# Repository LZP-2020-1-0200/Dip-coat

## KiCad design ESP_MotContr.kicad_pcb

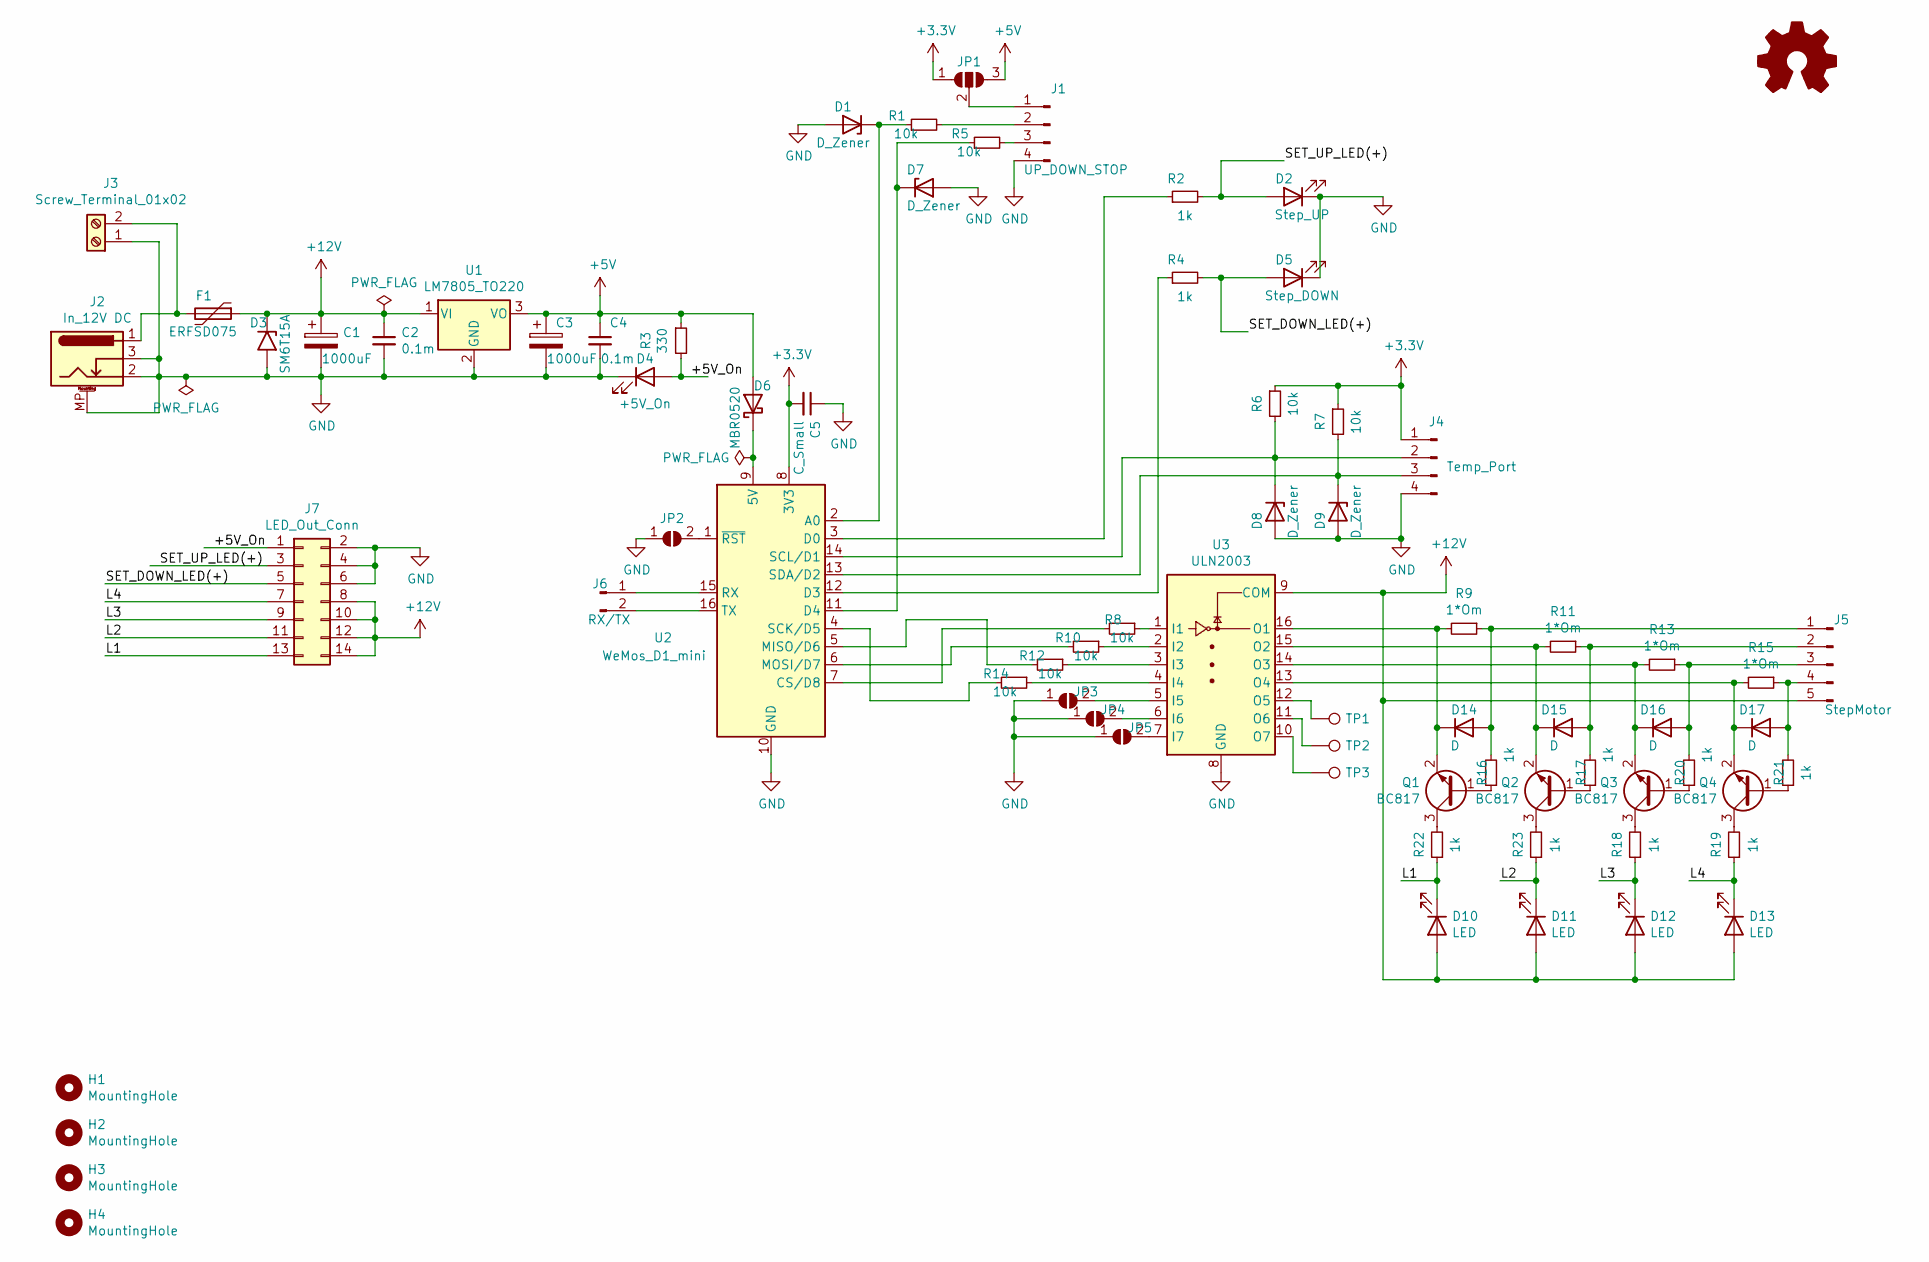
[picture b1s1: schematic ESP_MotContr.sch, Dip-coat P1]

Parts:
C1: 1000uF; CP_Elec_4x3
C2, C4: 0.1m; C_0805_2012Metric_Pad1.18x1.45mm_HandSolder
C3: 1000uF; CP_Elec_5x3
C5: C_Small; C_0805_2012Metric_Pad1.18x1.45mm_HandSolder
D1, D7, D8, D9: D_Zener; D_MiniMELF
D2: Step_UP; LED_0805_2012Metric_Pad1.15x1.40mm_HandSolder
D3: SM6T15A; D_SMB_Handsoldering
D4: +5V_On; LED_0805_2012Metric_Pad1.15x1.40mm_HandSolder
D5: Step_DOWN; LED_0805_2012Metric_Pad1.15x1.40mm_HandSolder
D6: MBR0520; D_SOD-123
D10, D11, D12, D13: LED; LED_0805_2012Metric_Pad1.15x1.40mm_HandSolder
D14, D15, D16, D17: D; D_0805_2012Metric_Pad1.15x1.40mm_HandSolder
F1: ERFSD075; Fuse_1812_4532Metric_Pad1.30x3.40mm_HandSolder
H1, H2, H3, H4: MountingHole; MountingHole_3.2mm_M3_DIN965
J1: UP_DOWN_STOP; JST_EH_S4B-EH_1x04_P2.50mm_Horizontal
J2: In_12V DC; BarrelJack_Horizontal
J3: Screw_Terminal_01x02; TerminalBlock_Altech_AK300-2_P5.00mm
J4: Temp_Port; JST_EH_S4B-EH_1x04_P2.50mm_Horizontal
J5: StepMotor; JST_EH_S5B-EH_1x05_P2.50mm_Horizontal
J6: RX/TX; JST_EH_B2B-EH-A_1x02_P2.50mm_Vertical
J7: LED_Out_Conn; PinHeader_2x07_P2.54mm_Vertical
JP1: SolderJumper_3_Open; SolderJumper-3_P1.3mm_Open_Pad1.0x1.5mm
JP2: SolderJumper_2_Open; SolderJumper-2_P1.3mm_Open_Pad1.0x1.5mm
JP3, JP4, JP5: InJP; SolderJumper-2_P1.3mm_Open_Pad1.0x1.5mm
Q1, Q2, Q3, Q4: BC817; SOT-23
R1, R5, R6, R7, R8, R10, R12, R14: 10k; R_0805_2012Metric_Pad1.20x1.40mm_HandSolder
R2, R4, R16, R17, R18, R19, R20, R21, R22, R23: 1k; R_0805_2012Metric_Pad1.20x1.40mm_HandSolder
R3: 330; R_0805_2012Metric_Pad1.20x1.40mm_HandSolder
R9, R11, R13, R15: 1*Om; R_0805_2012Metric_Pad1.20x1.40mm_HandSolder
TP1, TP2, TP3: TP; TestPoint_Pad_1.0x1.0mm
U1: LM7805_TO220; TO-220-3_Horizontal_TabDown
U2: WeMos_D1_mini; WEMOS_D1_mini_light
U3: ULN2003; DIP-16_W7.62mm_LongPads

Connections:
+3V3: C5.2, J4.1, JP1.1 (A), R6.1, R7.1, U2.8 (3V3)
+5V: C3.1, C4.1, D6.2 (A), JP1.3 (B), R3.1, U1.3 (VO)
+12V: C1.1, C2.1, D3.1 (A1), D10.2 (A), D11.2 (A), D12.2 (A), D13.2 (A), F1.1, J5.5, J7.8, J7.10, J7.12, J7.14, U1.1 (VI), U3.9 (COM)
/+5V_On: D4.2 (A), J7.1, R3.2
/L1: D10.1 (K), J7.13, R22.1
/L2: D11.1 (K), J7.11, R23.1
/L3: D12.1 (K), J7.9, R18.1
/L4: D13.1 (K), J7.7, R19.1
/SET_DOWN_LED(+): D5.2 (A), J7.5, R4.2
/SET_UP_LED(+): D2.2 (A), J7.3, R2.2
GND: C1.2, C2.2, C3.2, C4.2, C5.1, D1.2 (A), D2.1 (K), D3.2 (A2), D4.1 (K), D5.1 (K), D7.2 (A), D8.2 (A), D9.2 (A), J1.4, J2.2, J2.3, J2.MP (MountPin), J3.1, J4.4, J7.2, J7.4, J7.6, JP2.1 (A), JP3.1 (A), JP4.1 (A), JP5.1 (A), U1.2 (GND), U2.10 (GND), U3.8 (GND)
unnamed: D1.1 (K), R1.1, U2.2 (A0)
unnamed: D6.1 (K), U2.9 (5V)
unnamed: D7.1 (K), R5.1, U2.11 (D4)
unnamed: D8.1 (K), J4.2, R6.2, U2.14 (SCL/D1)
unnamed: D9.1 (K), J4.3, R7.2, U2.13 (SDA/D2)
unnamed: D14.1 (K), Q1.2 (E), R9.2, U3.16 (O1)
unnamed: D14.2 (A), J5.1, R9.1, R16.2
unnamed: D15.1 (K), Q2.2 (E), R11.2, U3.15 (O2)
unnamed: D15.2 (A), J5.2, R11.1, R17.2
unnamed: D16.1 (K), Q3.2 (E), R13.2, U3.14 (O3)
unnamed: D16.2 (A), J5.3, R13.1, R20.2
unnamed: D17.1 (K), Q4.2 (E), R15.2, U3.13 (O4)
unnamed: D17.2 (A), J5.4, R15.1, R21.2
unnamed: F1.2, J2.1, J3.2
unnamed: J1.1, JP1.2 (C)
unnamed: J1.2, R1.2
unnamed: J1.3, R5.2
unnamed: J6.1, U2.15 (RX)
unnamed: J6.2, U2.16 (TX)
unnamed: JP2.2 (B), U2.1 (~RST)
unnamed: JP3.2 (B), U3.5 (I5)
unnamed: JP4.2 (B), U3.6 (I6)
unnamed: JP5.2 (B), U3.7 (I7)
unnamed: Q1.1 (B), R16.1
unnamed: Q1.3 (C), R22.2
unnamed: Q2.1 (B), R17.1
unnamed: Q2.3 (C), R23.2
unnamed: Q3.1 (B), R20.1
unnamed: Q3.3 (C), R18.2
unnamed: Q4.1 (B), R21.1
unnamed: Q4.3 (C), R19.2
unnamed: R2.1, U2.3 (D0)
unnamed: R4.1, U2.12 (D3)
unnamed: R8.1, U3.1 (I1)
unnamed: R8.2, U2.7 (CS/D8)
unnamed: R10.1, U3.2 (I2)
unnamed: R10.2, U2.6 (MOSI/D7)
unnamed: R12.1, U3.3 (I3)
unnamed: R12.2, U2.5 (MISO/D6)
unnamed: R14.1, U3.4 (I4)
unnamed: R14.2, U2.4 (SCK/D5)
unnamed: TP1.1, U3.12 (O5)
unnamed: TP2.1, U3.11 (O6)
unnamed: TP3.1, U3.10 (O7)

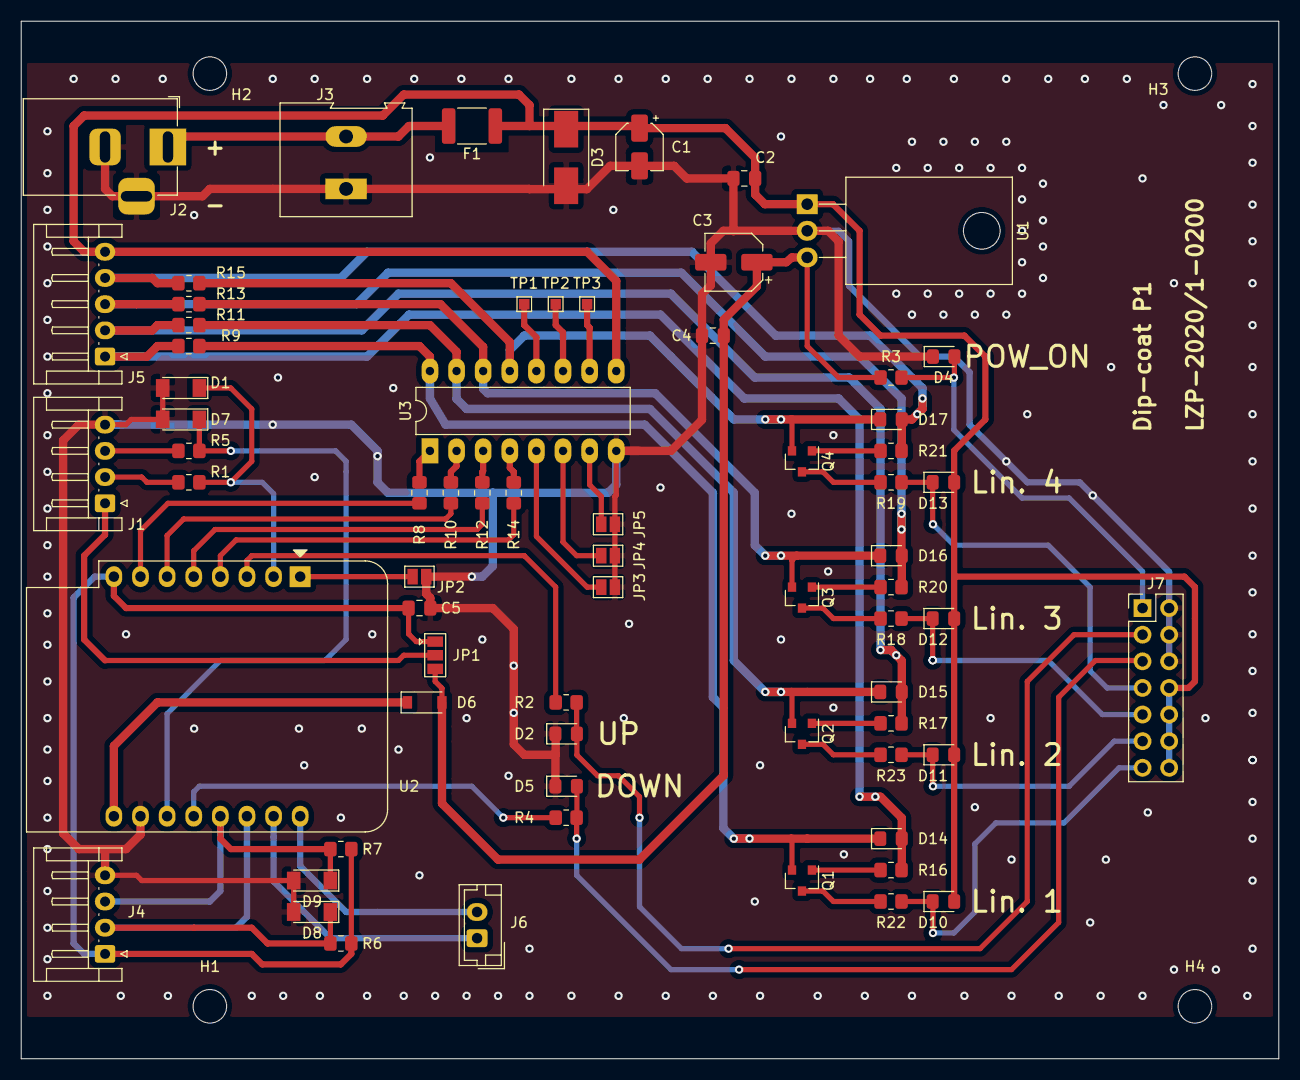
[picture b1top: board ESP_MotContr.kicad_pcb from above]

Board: 2 copper layers, 120.0 x 99.0 mm, 72 parts (0 on the bottom side), 55 nets.

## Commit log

2021-02-22 Pirmais izgatavotais prototips
